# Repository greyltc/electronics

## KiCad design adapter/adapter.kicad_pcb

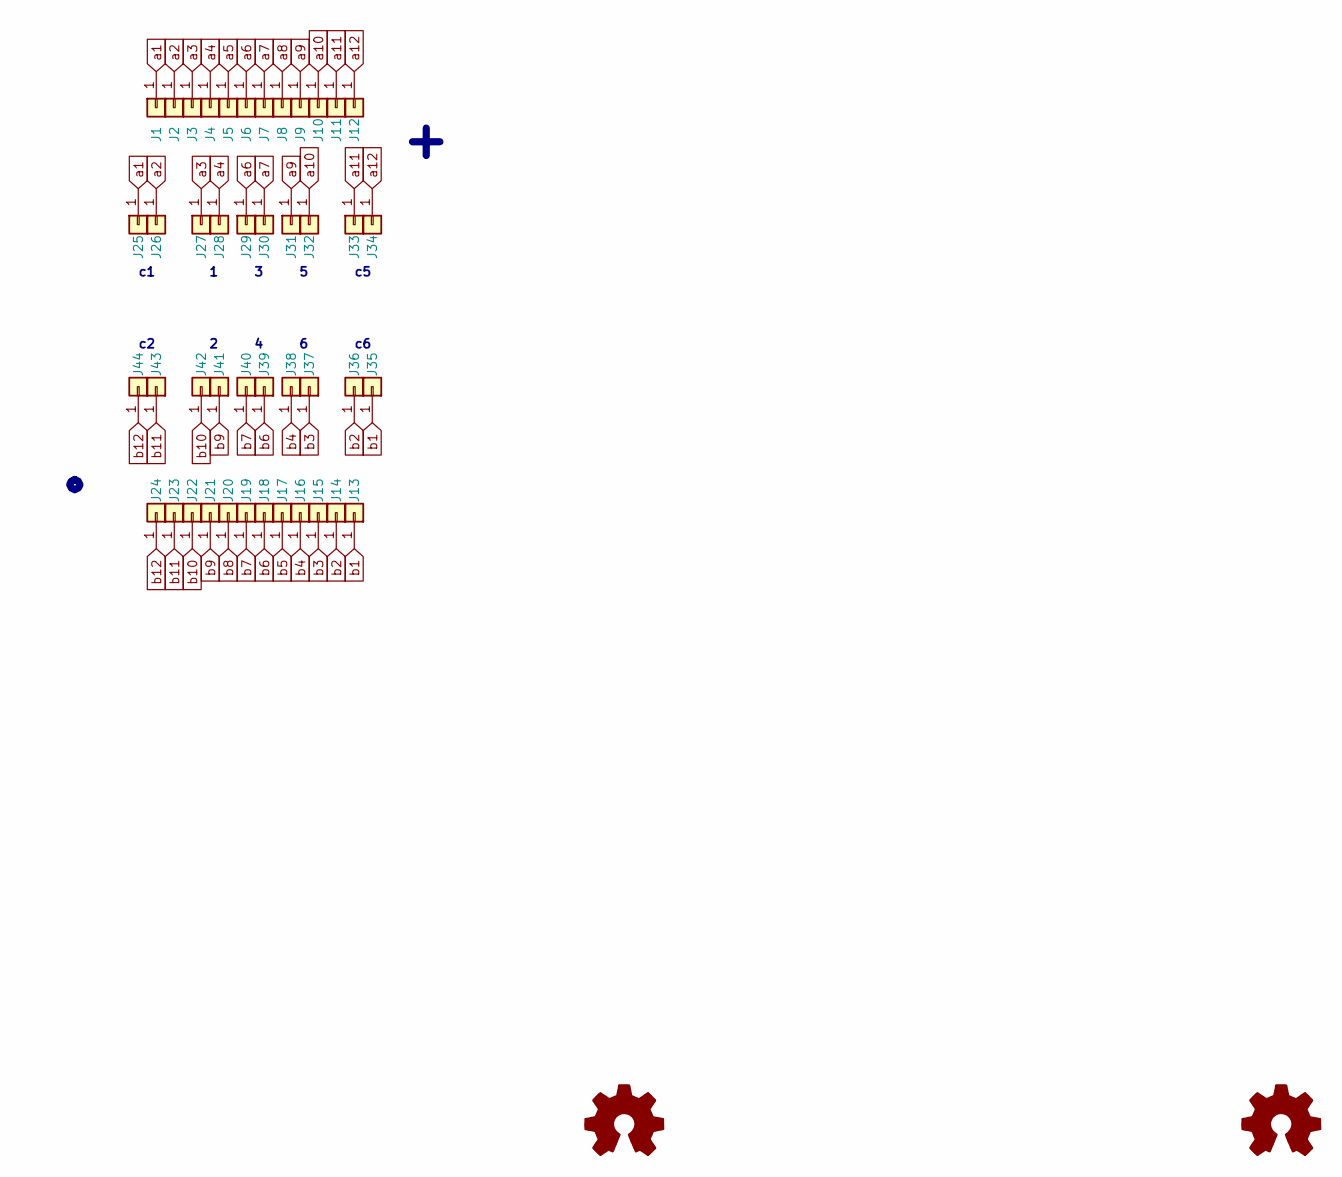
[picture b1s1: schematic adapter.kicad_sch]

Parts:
J1, J2, J3, J4, J5, J6, J7, J8, J9, J10, J11, J12, J13, J14, J15, J16, J17, J18, J19, J20, J21, J22, J23, J24: Conn_01x01; PTT-one-pin
J25, J26, J27, J28, J29, J30, J31, J32, J33, J34, J35, J36, J37, J38, J39, J40, J41, J42, J43, J44: Conn_01x01; 0921
LOGO1, LOGO2: Logo_Open_Hardware_Small; logo_small

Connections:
a1: J1.1, J25.1
a2: J2.1, J26.1
a3: J3.1, J27.1
a4: J4.1, J28.1
a5: J5.1
a6: J6.1, J29.1
a7: J7.1, J30.1
a8: J8.1
a9: J9.1, J31.1
a10: J10.1, J32.1
a11: J11.1, J33.1
a12: J12.1, J34.1
b1: J13.1, J35.1
b2: J14.1, J36.1
b3: J15.1, J37.1
b4: J16.1, J38.1
b5: J17.1
b6: J18.1, J39.1
b7: J19.1, J40.1
b8: J20.1
b9: J21.1, J41.1
b10: J22.1, J42.1
b11: J23.1, J43.1
b12: J24.1, J44.1

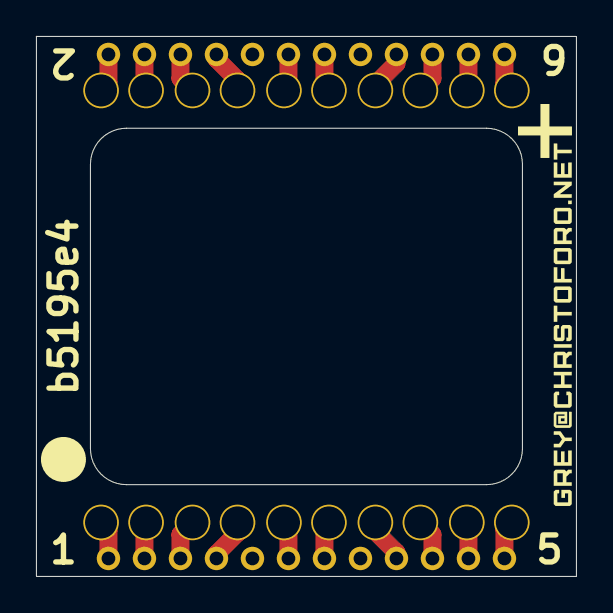
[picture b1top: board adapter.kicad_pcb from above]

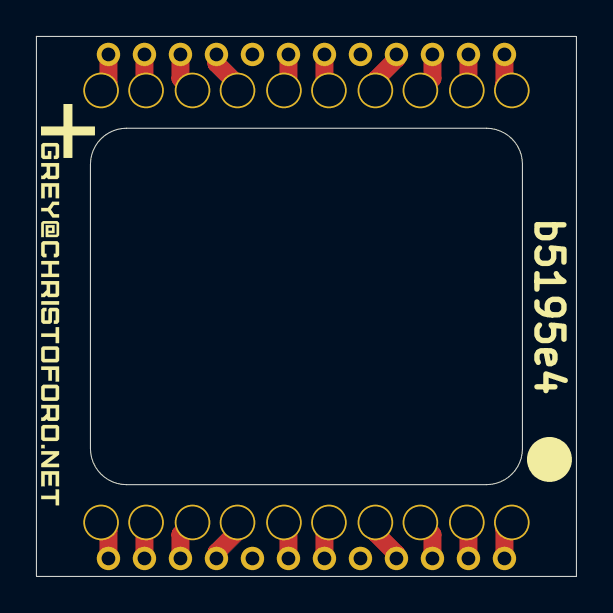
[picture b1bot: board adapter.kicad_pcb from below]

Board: 2 copper layers, 30.0 x 30.0 mm, 46 parts (25 on the bottom side), 20 nets.

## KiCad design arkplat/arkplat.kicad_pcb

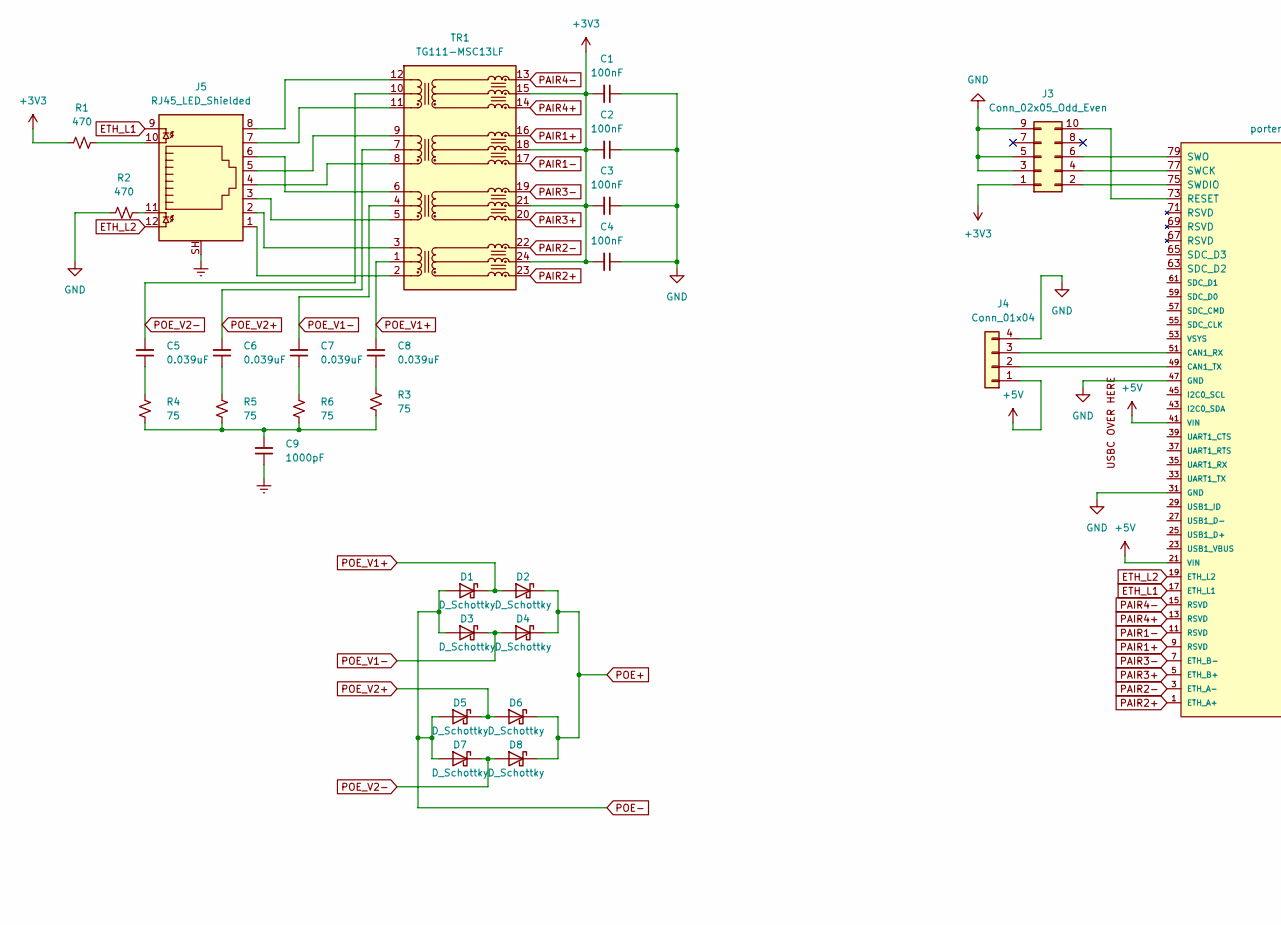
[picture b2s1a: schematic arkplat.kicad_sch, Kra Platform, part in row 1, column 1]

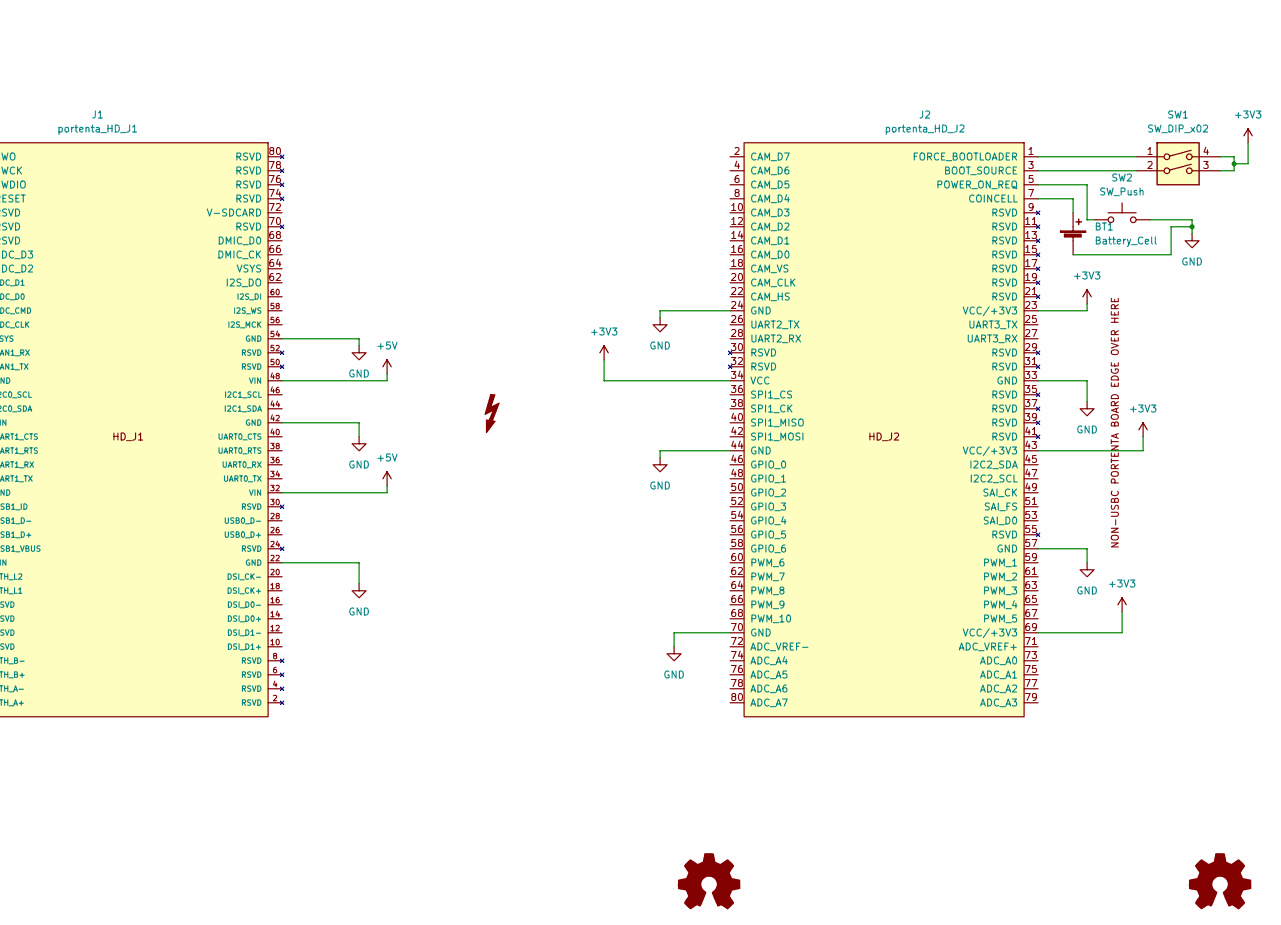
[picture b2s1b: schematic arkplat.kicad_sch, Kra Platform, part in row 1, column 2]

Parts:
BT1: Battery_Cell; BatteryHolder_Keystone_3034_1x20mm
C1, C2, C3, C4: 100nF; C_0603_1608Metric
C5, C6, C7, C8: 0.039uF; C_0603_1608Metric
C9: 1000pF; C_1206_3216Metric
D1, D2, D3, D4, D5, D6, D7, D8: D_Schottky; D_SMC
J1: portenta_HD_J1; DF40HC(3.5)-80DS-0.4V(51)
J2: portenta_HD_J2; DF40HC(3.5)-80DS-0.4V(51)
J3: Conn_02x05_Odd_Even; PinHeader_2x05_P1.27mm_Vertical_SMD
J4: Conn_01x04; PinHeader_1x04_P2.54mm_Vertical
J5: RJ45_LED_Shielded; RJ45_Amphenol_RJHSE538X
LOGO1, LOGO2: Logo_Open_Hardware_Small; logo
R1, R2: 470; R_0603_1608Metric
R3, R4, R5, R6: 75; R_0603_1608Metric
SW1: SW_DIP_x02; SW_DIP_SPSTx02_Slide_Omron_A6H-2101_W6.15mm_P1.27mm
SW2: SW_Push; SW_SPST_PTS645
SYM1: SYM_Flash_Small; portenta
TR1: TG111-MSC13LF; Transformer_Ethernet_HALO_TG111-MSC13

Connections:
+3V3: C1.2, C2.2, C3.2, C4.2, J2.23 (VCC/+3V3), J2.34 (VCC), J2.43 (VCC/+3V3), J2.69 (VCC/+3V3), J3.1, R1.1, SW1.3, SW1.4, TR1.15 (MCT4), TR1.18 (MCT3), TR1.21 (MCT2), TR1.24 (MTC1)
+5V: J1.21 (VIN), J1.32 (VIN), J1.41 (VIN), J1.48 (VIN), J4.1
ETH_L1: J1.17 (ETH_L1), J5.9
ETH_L2: J1.19 (ETH_L2), J5.12
Earth: C9.1, J5.SH
GND: BT1.2 (-), C1.1, C2.1, C3.1, C4.1, J1.22 (GND), J1.31 (GND), J1.42 (GND), J1.47 (GND), J1.54 (GND), J2.24 (GND), J2.33 (GND), J2.44 (GND), J2.57 (GND), J2.70 (GND), J3.3, J3.5, J3.9, J4.4, R2.1, SW2.2
unnamed: BT1.1 (+), J2.7 (COINCELL)
unnamed: C5.1, R4.2
unnamed: C6.1, R5.2
unnamed: C7.1, R6.2
unnamed: C8.1, R3.2
unnamed: J1.49 (CAN1_TX), J4.2
unnamed: J1.51 (CAN1_RX), J4.3
unnamed: J1.73 (RESET), J3.10
unnamed: J1.75 (SWDIO), J3.2
unnamed: J1.77 (SWCK), J3.4
unnamed: J1.79 (SWO), J3.6
unnamed: J2.1 (FORCE_BOOTLOADER), SW1.1
unnamed: J2.3 (BOOT_SOURCE), SW1.2
unnamed: J2.5 (POWER_ON_REQ), SW2.1
unnamed: J5.1, TR1.2 (TD1+)
unnamed: J5.2, TR1.3 (TD1-)
unnamed: J5.3, TR1.5 (TD2+)
unnamed: J5.4, TR1.8 (TD3+)
unnamed: J5.5, TR1.9 (TD3-)
unnamed: J5.6, TR1.6 (TD2-)
unnamed: J5.7, TR1.11 (TD4+)
unnamed: J5.8, TR1.12 (TD4-)
unnamed: J5.10, R1.2
unnamed: J5.11, R2.2
unnamed: C9.2, R3.1, R4.1, R5.1, R6.1
PAIR1+: J1.9 (RSVD), TR1.16 (MTX3-)
PAIR1-: J1.11 (RSVD), TR1.17 (MTX3+)
PAIR2+: J1.1 (ETH_A+), TR1.23 (MTX1+)
PAIR2-: J1.3 (ETH_A-), TR1.22 (MTX1-)
PAIR3+: J1.5 (ETH_B+), TR1.20 (MTX2+)
PAIR3-: J1.7 (ETH_B-), TR1.19 (MTX2-)
PAIR4+: J1.13 (RSVD), TR1.14 (MX4+)
PAIR4-: J1.15 (RSVD), TR1.13 (MX4-)
POE+: D2.1 (K), D4.1 (K), D6.1 (K), D8.1 (K)
POE-: D1.2 (A), D3.2 (A), D5.2 (A), D7.2 (A)
POE_V1+: C8.2, D1.1 (K), D2.2 (A), TR1.1 (TCT1)
POE_V1-: C7.2, D3.1 (K), D4.2 (A), TR1.4 (TCT2)
POE_V2+: C6.2, D5.1 (K), D6.2 (A), TR1.7 (TCT3)
POE_V2-: C5.2, D7.1 (K), D8.2 (A), TR1.10 (TCT4)

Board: 2 copper layers, 35 parts (1 on the bottom side), 45 nets, no tracks yet.

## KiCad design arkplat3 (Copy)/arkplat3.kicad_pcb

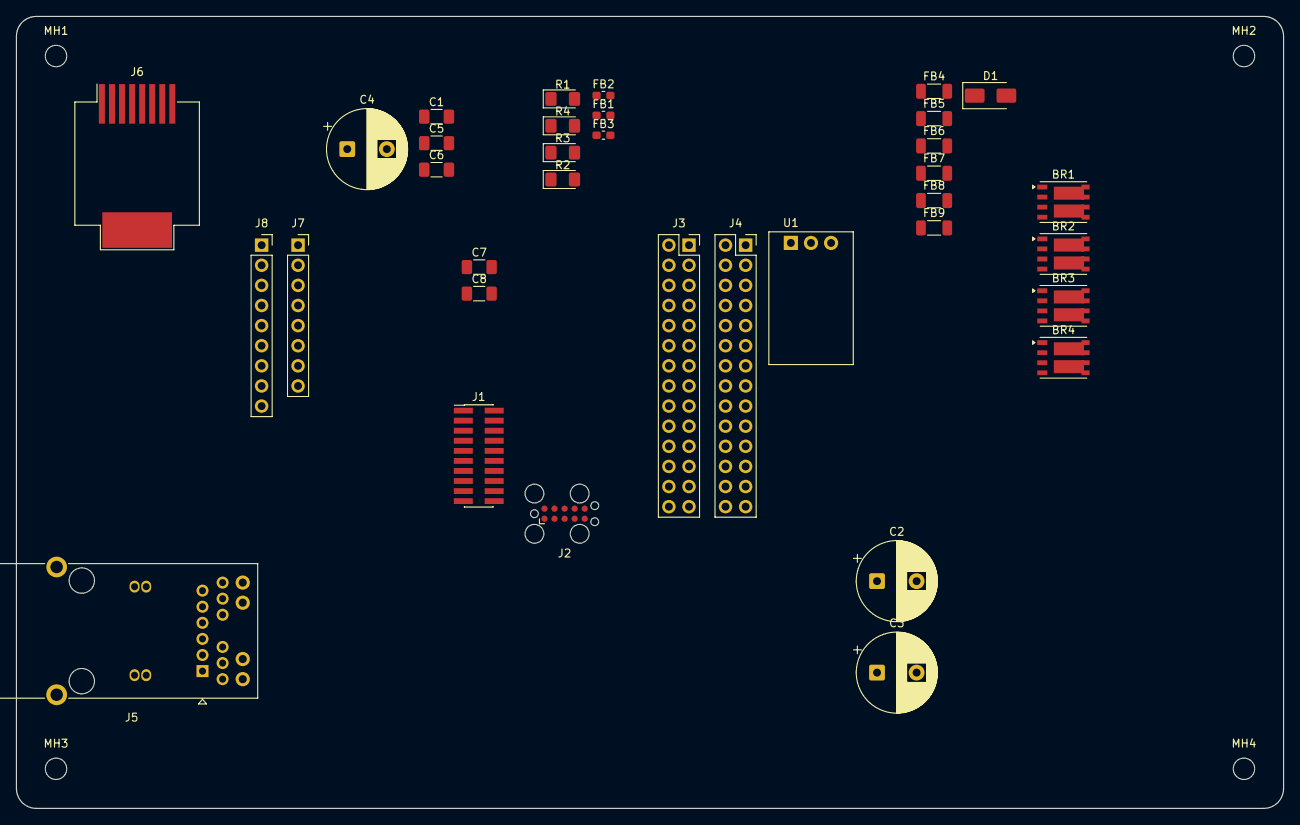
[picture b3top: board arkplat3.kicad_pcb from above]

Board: 2 copper layers, 160.0 x 100.0 mm, 39 parts (0 on the bottom side), 35 nets, no tracks yet.

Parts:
BR1, BR2, BR3, BR4: Conn_01x06; PowerPAK_SO-8_Dual
C1: 1000pF; C_1206_3216Metric_Pad1.33x1.80mm_HandSolder
C2, C3: 1000uF; CP_Radial_D10.0mm_P5.00mm
C4: 470uF; CP_Radial_D10.0mm_P5.00mm
C5: 10uF; C_1206_3216Metric_Pad1.33x1.80mm_HandSolder
C6: 100nF; C_1206_3216Metric_Pad1.33x1.80mm_HandSolder
C7, C8: 4.7nF; C_1206_3216Metric_Pad1.33x1.80mm_HandSolder
D1: SMAJ58A; D_SMA
FB1, FB2, FB3: FerriteBead_Small; L_0603_1608Metric_Pad1.05x0.95mm_HandSolder
FB4, FB5, FB6, FB7, FB8, FB9: FerriteBead; L_1206_3216Metric_Pad1.22x1.90mm_HandSolder
J1: Conn_02x10_Odd_Even; PinHeader_2x10_P1.27mm_Vertical_SMD
J2: J-LINK NEEDLE; Tag-Connect_TC2050-IDC-FP_2x05_P1.27mm_Vertical
J3, J4: Conn_02x14_Odd_Even; PinSocket_2x14_P2.54mm_Vertical
J5: RJ45_JK00177; RJ45_Pulse_JK00177NL_Horizontal
J6: RJ45_Shielded; RJ45_Molex_0855135013_Vertical
J7: AG5800IN; PinSocket_1x08_P2.54mm_Vertical
J8: AG5800OUT; PinSocket_1x09_P2.54mm_Vertical
MH1, MH2, MH3, MH4: MountingHole; MountingHole_2.7mm_M2.5_ISO14580
R1, R2, R3, R4: 75R; LED_1206_3216Metric_Pad1.42x1.75mm_HandSolder
U1: OKI-78SR-3.3_1.5-W36H-C; Converter_DCDC_Murata_OKI-78SR_Horizontal

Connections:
/0V1: C2.2, C3.2, C4.2, C5.1, C6.1, J2.3, J4.21, J4.22, J8.2, J8.3, J8.6, J8.7, U1.2 (GND)
/3V3: J4.23, J4.24
/+5V: J4.27, J4.28
/AREF: J3.27, J3.28
/CIPO: J4.9, J4.10
/CK: J4.7, J4.8
/COPI: J4.5, J4.6
/CS: J4.3, J4.4
/DAC: J3.13, J3.14
/FAN_PWM: J3.1, J3.2
/FAN_TACH: J3.3, J3.4
/SCL3: J4.13, J4.14
/SDA3: J4.11, J4.12
/VIN: J4.25, J4.26, U1.3 (OUT)
/VOUT1: C2.1, C3.1, C4.1, C5.2, C6.2, J8.4, J8.5, J8.8, J8.9, U1.1 (IN)
/~RST: J4.19, J4.20
unnamed: BR1.1, BR1.2
unnamed: BR1.3, BR1.4
unnamed: BR3.1, BR3.2
unnamed: BR3.3, BR3.4
unnamed: BR4.1, BR4.2
unnamed: BR4.3, BR4.4
unnamed: J3.5, J3.6
unnamed: J3.7, J3.8
unnamed: J3.9, J3.10
unnamed: J3.11, J3.12
unnamed: J3.15, J3.16
unnamed: J3.17, J3.18
unnamed: J3.19, J3.20
unnamed: J3.21, J3.22
unnamed: J3.23, J3.24
unnamed: J3.25, J3.26
unnamed: J4.1, J4.2
unnamed: J4.15, J4.16
unnamed: J4.17, J4.18

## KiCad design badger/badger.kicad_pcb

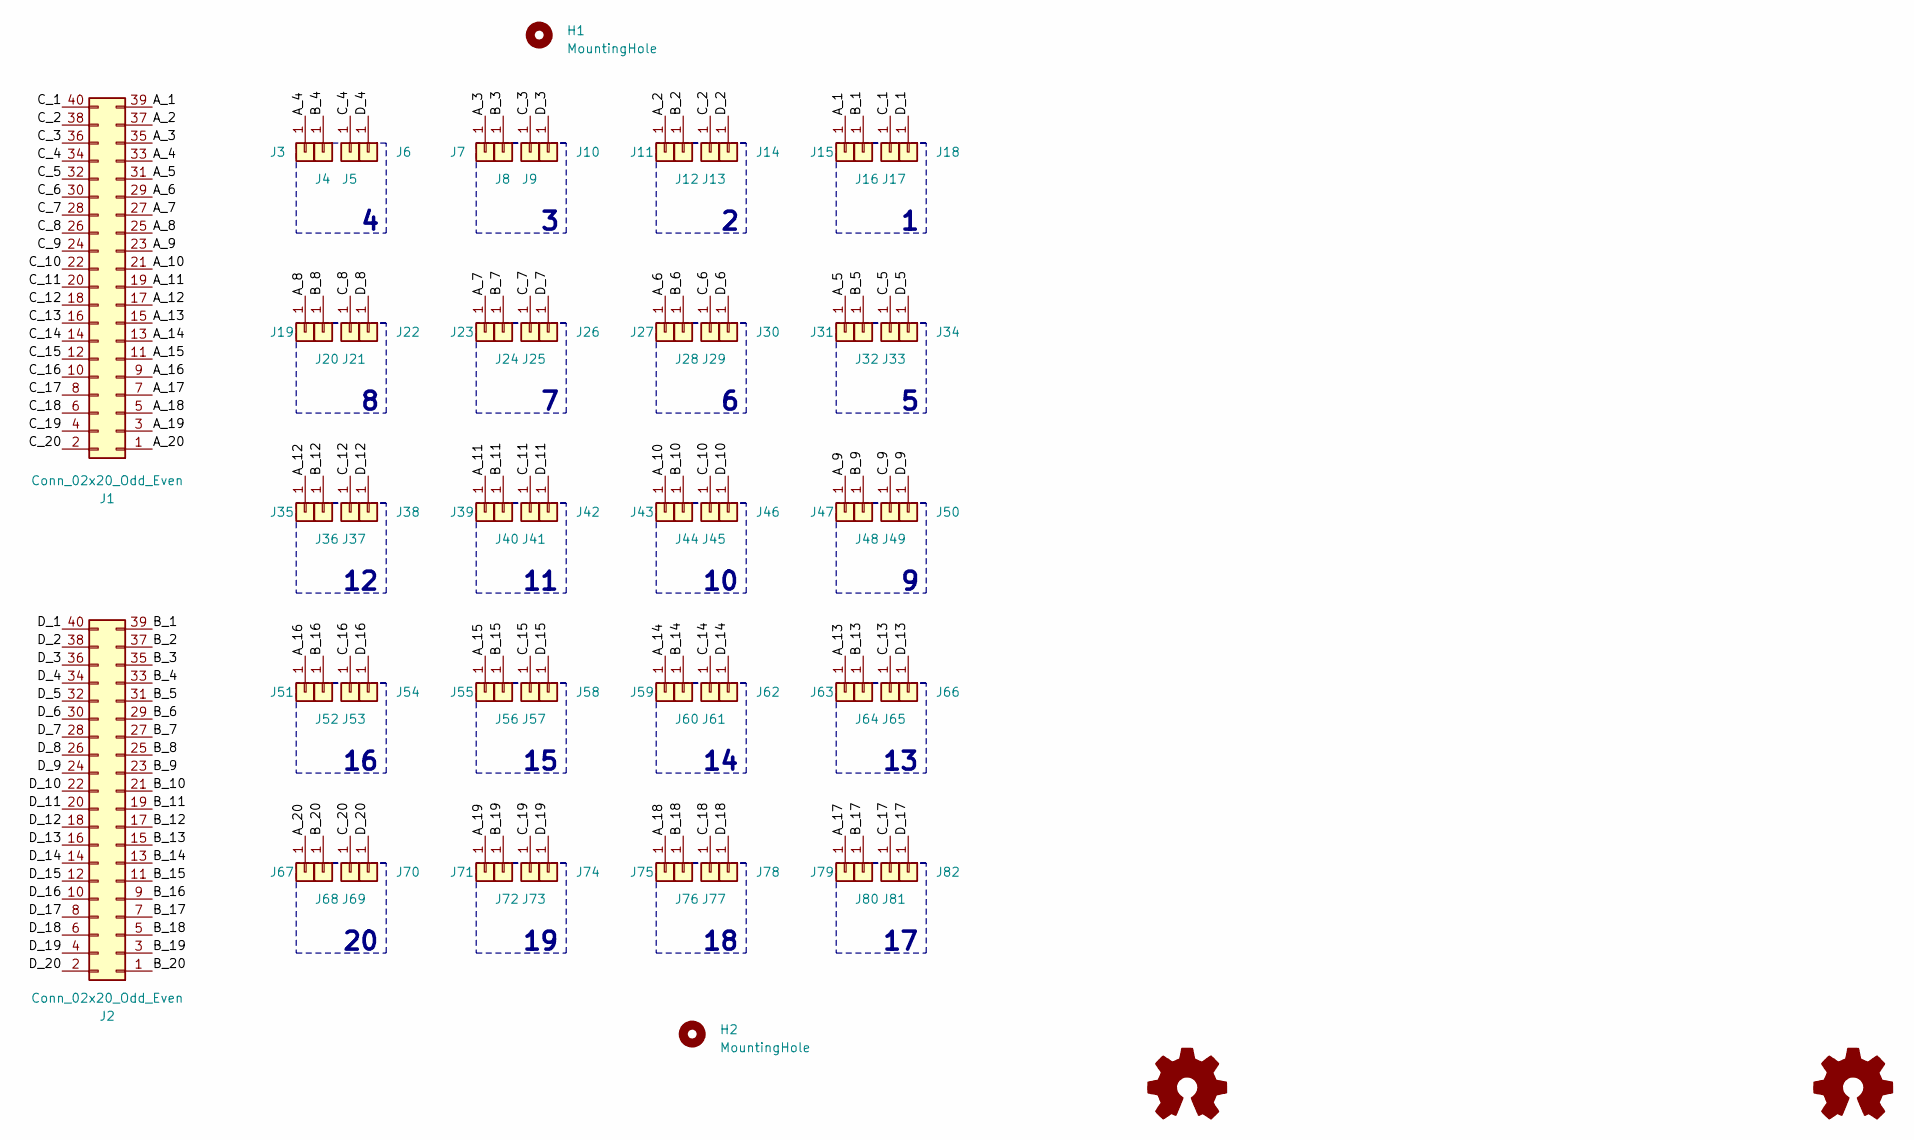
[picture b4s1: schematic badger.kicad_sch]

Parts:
H1, H2: MountingHole; MountingHole_7.1mm
J1: Conn_02x20_Odd_Even; HTSS-120-04-G-D-RA; mfg_part HTSS-120-04-G-D-RA
J2: Conn_02x20_Odd_Even; HTSS-120-04-G-D-RA; mgf_part HTSS-120-04-G-D-RA
J3, J4, J5, J6, J7, J8, J9, J10, J11, J12, J13, J14, J15, J16, J17, J18, J19, J20, J21, J22, J23, J24, J25, J26, J27, J28, J29, J30, J31, J32, J33, J34, J35, J36, J37, J38, J39, J40, J41, J42, J43, J44, J45, J46, J47, J48, J49, J50, J51, J52, J53, J54, J55, J56, J57, J58, J59, J60, J61, J62, J63, J64, J65, J66, J67, J68, J69, J70, J71, J72, J73, J74, J75, J76, J77, J78, J79, J80, J81, J82: Conn_01x01; 0921
LOGO1, LOGO2: Logo_Open_Hardware_Small; site_small

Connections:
/A_1: J1.39, J15.1
/A_2: J1.37, J11.1
/A_3: J1.35, J7.1
/A_4: J1.33, J3.1
/A_5: J1.31, J31.1
/A_6: J1.29, J27.1
/A_7: J1.27, J23.1
/A_8: J1.25, J19.1
/A_9: J1.23, J47.1
/A_10: J1.21, J43.1
/A_11: J1.19, J39.1
/A_12: J1.17, J35.1
/A_13: J1.15, J63.1
/A_14: J1.13, J59.1
/A_15: J1.11, J55.1
/A_16: J1.9, J51.1
/A_17: J1.7, J79.1
/A_18: J1.5, J75.1
/A_19: J1.3, J71.1
/A_20: J1.1, J67.1
/B_1: J2.39, J16.1
/B_2: J2.37, J12.1
/B_3: J2.35, J8.1
/B_4: J2.33, J4.1
/B_5: J2.31, J32.1
/B_6: J2.29, J28.1
/B_7: J2.27, J24.1
/B_8: J2.25, J20.1
/B_9: J2.23, J48.1
/B_10: J2.21, J44.1
/B_11: J2.19, J40.1
/B_12: J2.17, J36.1
/B_13: J2.15, J64.1
/B_14: J2.13, J60.1
/B_15: J2.11, J56.1
/B_16: J2.9, J52.1
/B_17: J2.7, J80.1
/B_18: J2.5, J76.1
/B_19: J2.3, J72.1
/B_20: J2.1, J68.1
/C_1: J1.40, J17.1
/C_2: J1.38, J13.1
/C_3: J1.36, J9.1
/C_4: J1.34, J5.1
/C_5: J1.32, J33.1
/C_6: J1.30, J29.1
/C_7: J1.28, J25.1
/C_8: J1.26, J21.1
/C_9: J1.24, J49.1
/C_10: J1.22, J45.1
/C_11: J1.20, J41.1
/C_12: J1.18, J37.1
/C_13: J1.16, J65.1
/C_14: J1.14, J61.1
/C_15: J1.12, J57.1
/C_16: J1.10, J53.1
/C_17: J1.8, J81.1
/C_18: J1.6, J77.1
/C_19: J1.4, J73.1
/C_20: J1.2, J69.1
/D_1: J2.40, J18.1
/D_2: J2.38, J14.1
/D_3: J2.36, J10.1
/D_4: J2.34, J6.1
/D_5: J2.32, J34.1
/D_6: J2.30, J30.1
/D_7: J2.28, J26.1
/D_8: J2.26, J22.1
/D_9: J2.24, J50.1
/D_10: J2.22, J46.1
/D_11: J2.20, J42.1
/D_12: J2.18, J38.1
/D_13: J2.16, J66.1
/D_14: J2.14, J62.1
/D_15: J2.12, J58.1
/D_16: J2.10, J54.1
/D_17: J2.8, J82.1
/D_18: J2.6, J78.1
/D_19: J2.4, J74.1
/D_20: J2.2, J70.1

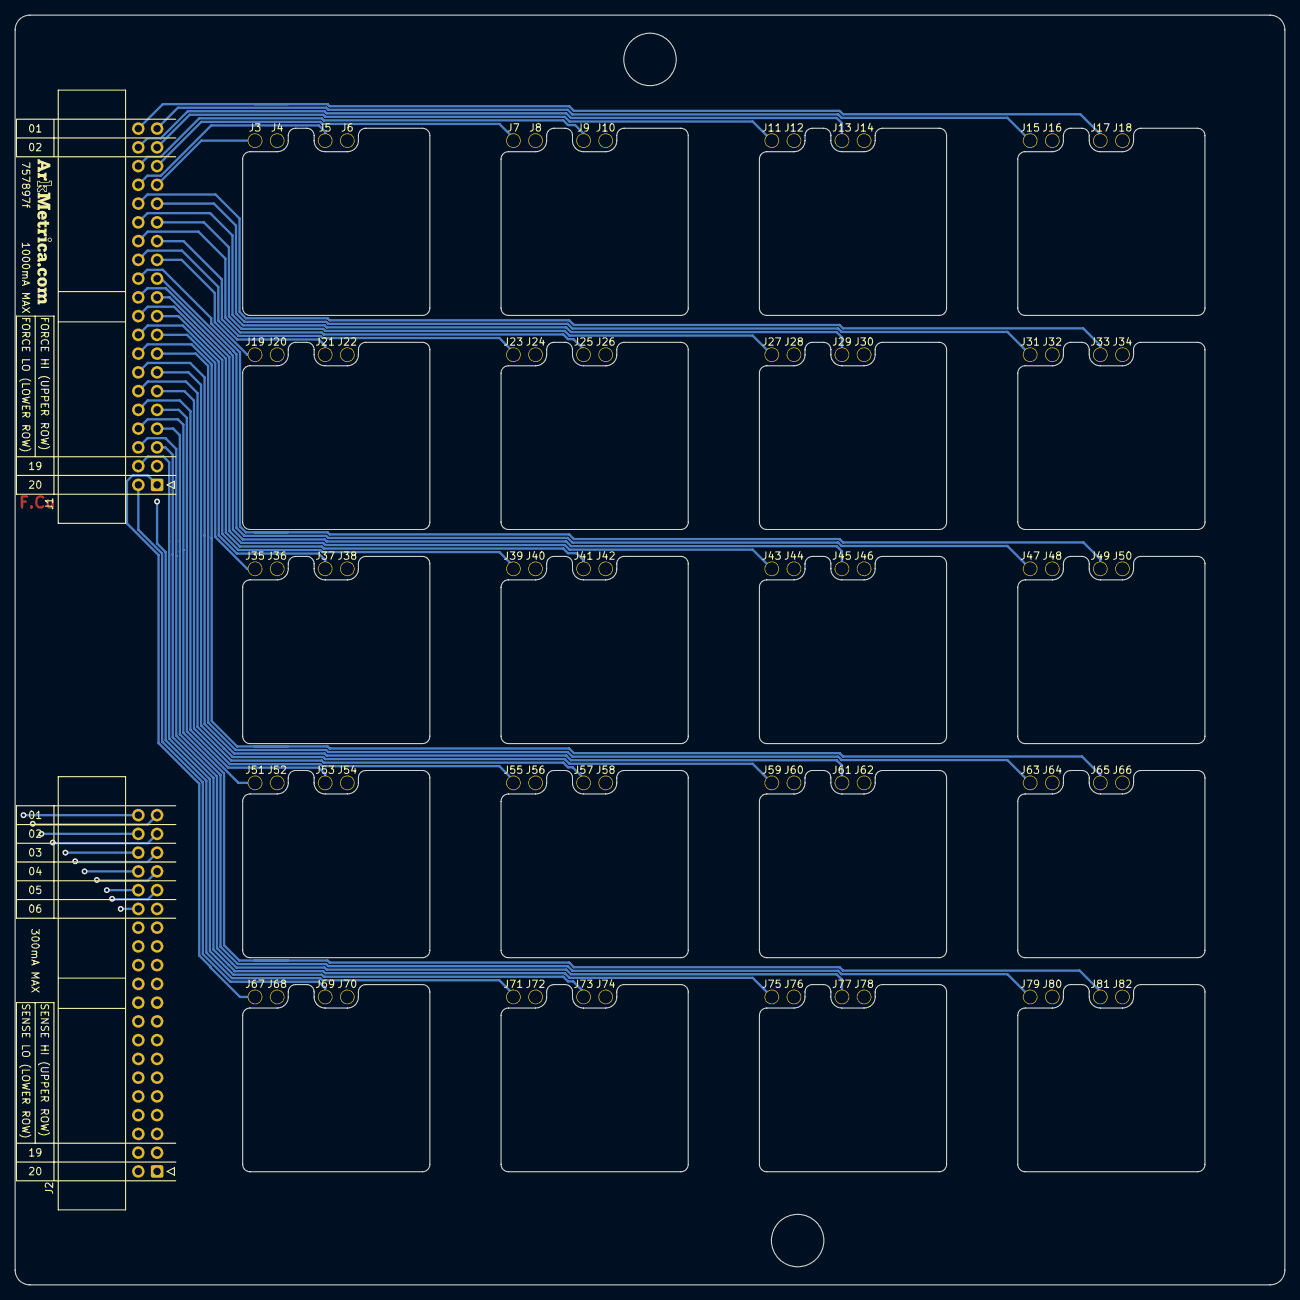
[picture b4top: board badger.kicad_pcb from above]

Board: 4 copper layers, 172.0 x 172.0 mm, 86 parts (1 on the bottom side), 80 nets.
